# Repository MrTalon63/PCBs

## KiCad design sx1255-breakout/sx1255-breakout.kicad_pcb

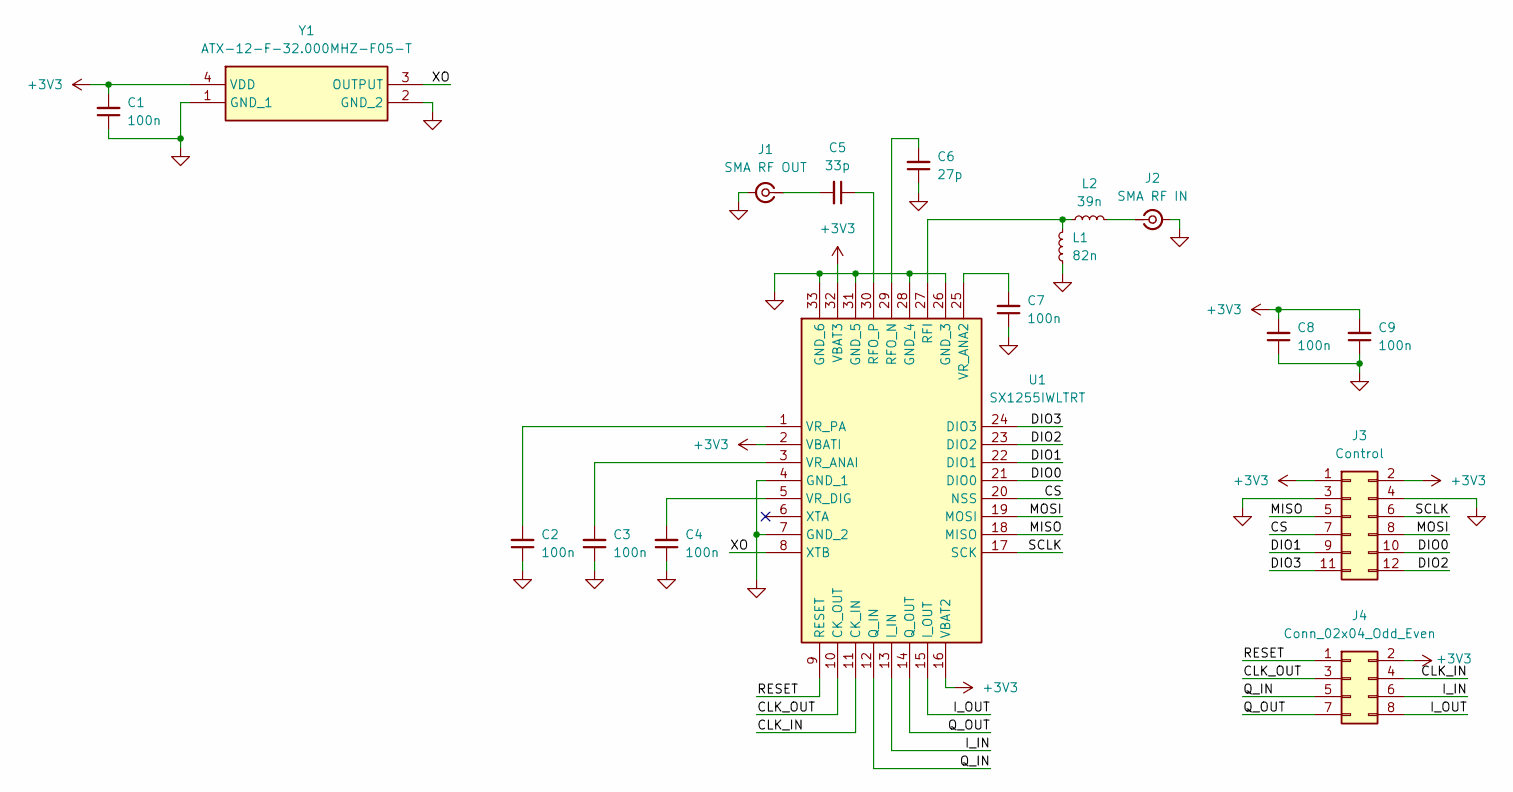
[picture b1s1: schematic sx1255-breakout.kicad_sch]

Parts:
C1, C2, C3, C4, C7, C8, C9: 100n; C_0402_1005Metric
C5: 33p; C_0402_1005Metric
C6: 27p; C_0402_1005Metric
J1: SMA RF OUT; SMA_Samtec_SMA-J-P-H-ST-EM1_EdgeMount
J2: SMA RF IN; SMA_Samtec_SMA-J-P-H-ST-EM1_EdgeMount
J3: Control; PinSocket_2x06_P2.54mm_Vertical
J4: Conn_02x04_Odd_Even; PinSocket_2x04_P2.54mm_Vertical
L1: 82n; L_0402_1005Metric
L2: 39n; L_0402_1005Metric
U1: SX1255IWLTRT; QFN50P500X500X80-33N-D; Mouser Part Number 947-SX1255IWLTRT
Y1: ATX-12-F-32.000MHZ-F05-T; ATX12F32000MHZF05T; Mouser Part Number 815-ATX12F32000MF05T

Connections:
+3V3: C1.2, C8.2, C9.2, J3.1, J3.2, J4.2, U1.2 (VBATI), U1.16 (VBAT2), U1.32 (VBAT3), Y1.4 (VDD)
/CLK_IN: J4.4, U1.11 (CK_IN)
/CLK_OUT: J4.3, U1.10 (CK_OUT)
/CS: J3.7, U1.20 (NSS)
/DIO0: J3.10, U1.21 (DIO0)
/DIO1: J3.9, U1.22 (DIO1)
/DIO2: J3.12, U1.23 (DIO2)
/DIO3: J3.11, U1.24 (DIO3)
/I_IN: J4.6, U1.13 (I_IN)
/I_OUT: J4.8, U1.15 (I_OUT)
/MISO: J3.5, U1.18 (MISO)
/MOSI: J3.8, U1.19 (MOSI)
/Q_IN: J4.5, U1.12 (Q_IN)
/Q_OUT: J4.7, U1.14 (Q_OUT)
/RESET: J4.1, U1.9 (RESET)
/SCLK: J3.6, U1.17 (SCK)
/XO: U1.8 (XTB), Y1.3 (OUTPUT)
GND: C1.1, C2.1, C3.1, C4.1, C6.1, C7.1, C8.1, C9.1, J1.2 (Ext), J2.2 (Ext), J3.3, J3.4, L1.1, U1.4 (GND_1), U1.7 (GND_2), U1.26 (GND_3), U1.28 (GND_4), U1.31 (GND_5), U1.33 (GND_6), Y1.1 (GND_1), Y1.2 (GND_2)
unnamed: C5.2, J1.1 (In)
unnamed: J2.1 (In), L2.2
unnamed: L1.2, L2.1, U1.27 (RFI)
unnamed: C6.2, U1.29 (RFO_N)
unnamed: C5.1, U1.30 (RFO_P)
unnamed: C7.2, U1.25 (VR_ANA2)
unnamed: C3.2, U1.3 (VR_ANAI)
unnamed: C4.2, U1.5 (VR_DIG)
unnamed: C2.2, U1.1 (VR_PA)

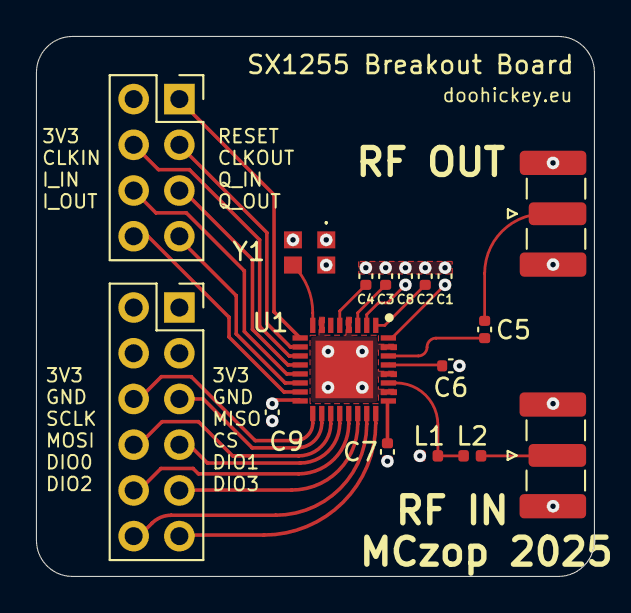
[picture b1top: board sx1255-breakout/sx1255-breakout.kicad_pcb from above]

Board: 6 copper layers, 31.0 x 30.0 mm, 17 parts (0 on the bottom side), 27 nets.

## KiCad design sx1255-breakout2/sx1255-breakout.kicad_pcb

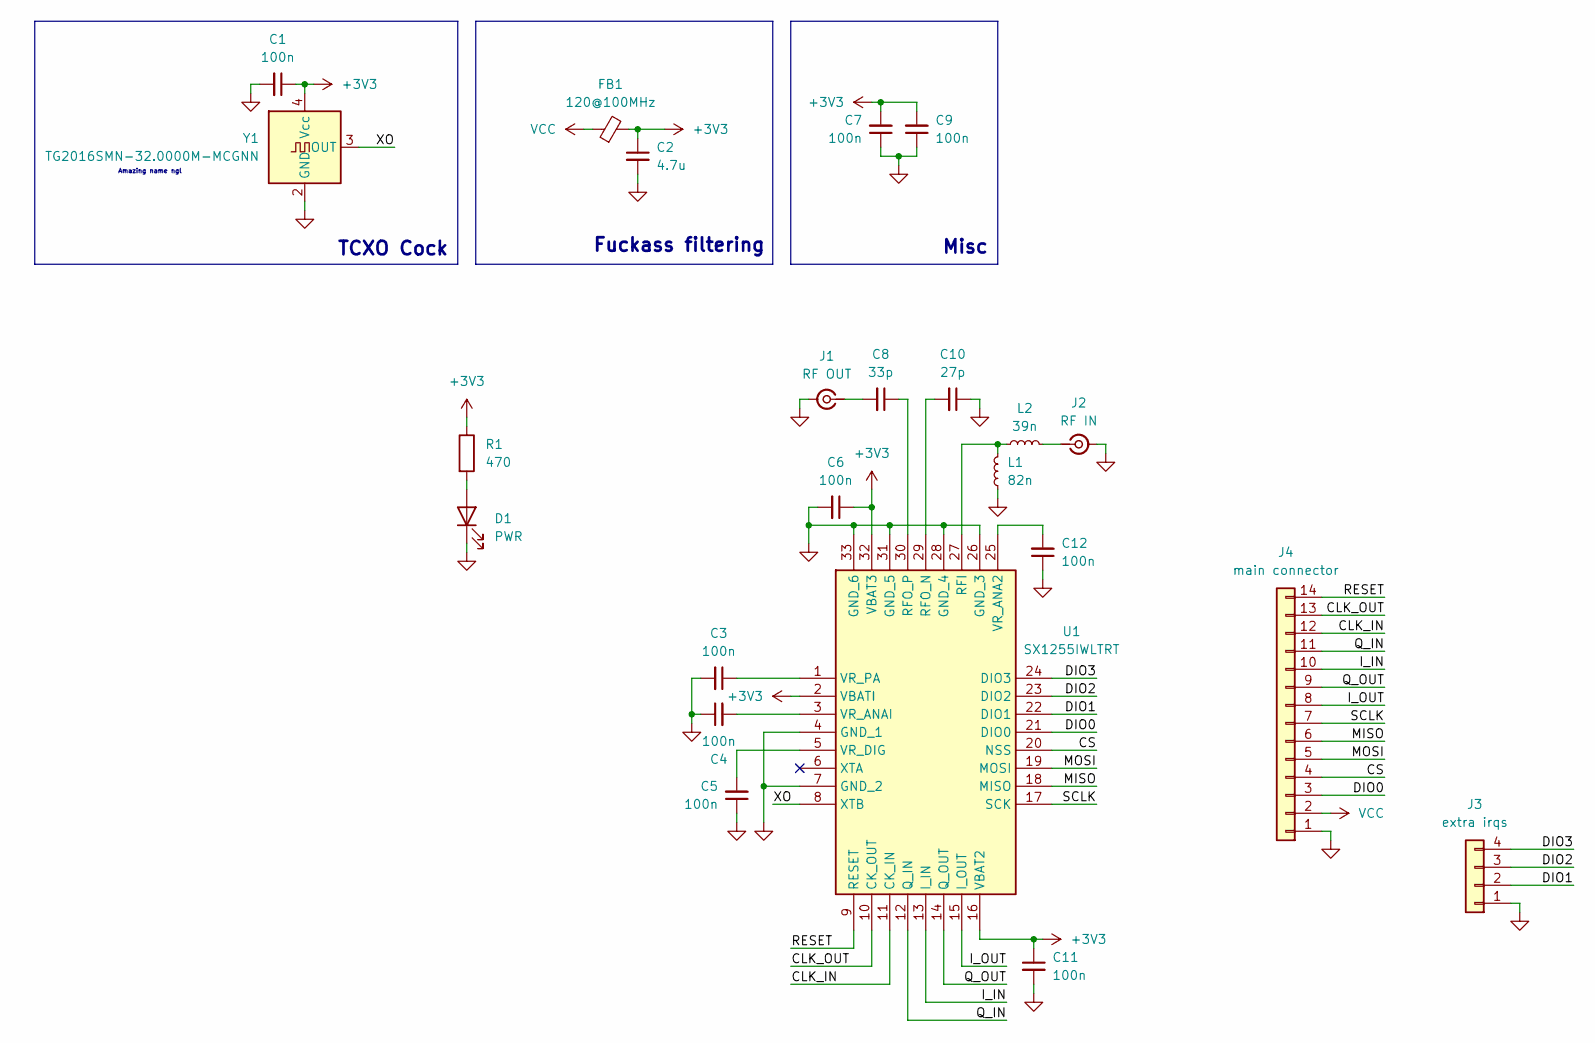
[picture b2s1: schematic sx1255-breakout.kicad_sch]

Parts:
C1, C3, C4, C5, C6, C7, C9, C11, C12: 100n; C_0603_1608Metric_Pad1.08x0.95mm_HandSolder
C2: 4.7u; C_0805_2012Metric_Pad1.18x1.45mm_HandSolder
C8: 33p; C_0603_1608Metric_Pad1.08x0.95mm_HandSolder
C10: 27p; C_0603_1608Metric_Pad1.08x0.95mm_HandSolder
D1: PWR; LED_0805_2012Metric_Pad1.15x1.40mm_HandSolder
FB1: 120@100MHz; L_0603_1608Metric_Pad1.05x0.95mm_HandSolder
J1: RF OUT; SMA_Samtec_SMA-J-P-H-ST-EM1_EdgeMount
J2: RF IN; SMA_Samtec_SMA-J-P-H-ST-EM1_EdgeMount
J3: extra irqs; PinHeader_1x04_P2.54mm_Vertical
J4: main connector; PinHeader_1x14_P2.54mm_Vertical
L1: 82n; L_0603_1608Metric_Pad1.05x0.95mm_HandSolder
L2: 39n; L_0603_1608Metric_Pad1.05x0.95mm_HandSolder
R1: 470; R_0603_1608Metric_Pad0.98x0.95mm_HandSolder
U1: SX1255IWLTRT; QFN-32-1EP_5x5mm_P0.5mm_EP3.1x3.1mm; Mouser Part Number 947-SX1255IWLTRT
Y1: TG2016SMN-32.0000M-MCGNN; Crystal_SMD_2016-4Pin_2.0x1.6mm

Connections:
+3V3: C1.1, C2.1, C6.1, C7.2, C9.2, C11.1, FB1.2, R1.1, U1.2 (VBATI), U1.16 (VBAT2), U1.32 (VBAT3), Y1.4 (Vcc)
/CLK_IN: J4.12, U1.11 (CK_IN)
/CLK_OUT: J4.13, U1.10 (CK_OUT)
/CS: J4.4, U1.20 (NSS)
/DIO0: J4.3, U1.21 (DIO0)
/DIO1: J3.2, U1.22 (DIO1)
/DIO2: J3.3, U1.23 (DIO2)
/DIO3: J3.4, U1.24 (DIO3)
/I_IN: J4.10, U1.13 (I_IN)
/I_OUT: J4.8, U1.15 (I_OUT)
/MISO: J4.6, U1.18 (MISO)
/MOSI: J4.5, U1.19 (MOSI)
/Q_IN: J4.11, U1.12 (Q_IN)
/Q_OUT: J4.9, U1.14 (Q_OUT)
/RESET: J4.14, U1.9 (RESET)
/SCLK: J4.7, U1.17 (SCK)
/XO: U1.8 (XTB), Y1.3 (OUT)
GND: C1.2, C2.2, C3.2, C4.1, C5.1, C6.2, C7.1, C9.1, C10.1, C11.2, C12.1, D1.1 (K), J1.2 (Ext), J2.2 (Ext), J3.1, J4.1, L1.1, U1.4 (GND_1), U1.7 (GND_2), U1.26 (GND_3), U1.28 (GND_4), U1.31 (GND_5), U1.33 (GND_6), Y1.2 (GND); also elsewhere on the board
unnamed 18: D1.2 (A), R1.2; also elsewhere on the board
unnamed: C8.2, J1.1 (In)
unnamed: J2.1 (In), L2.2
unnamed: L1.2, L2.1, U1.27 (RFI)
unnamed: C10.2, U1.29 (RFO_N)
unnamed: C8.1, U1.30 (RFO_P)
unnamed: C12.2, U1.25 (VR_ANA2)
unnamed: C4.2, U1.3 (VR_ANAI)
unnamed: C5.2, U1.5 (VR_DIG)
unnamed: C3.1, U1.1 (VR_PA)
VCC: FB1.1, J4.2

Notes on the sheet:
Misc
Amazing name ngl
Fuckass filtering
TCXO Cock

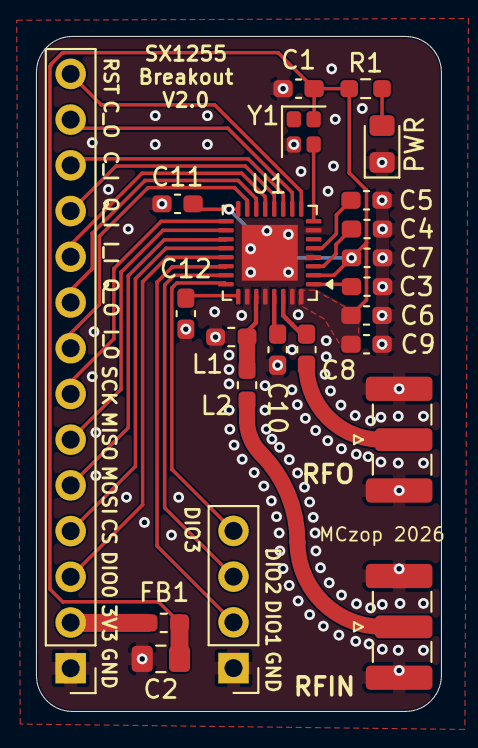
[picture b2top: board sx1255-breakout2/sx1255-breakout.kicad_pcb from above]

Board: 2 copper layers, 22.5 x 37.5 mm, 23 parts (0 on the bottom side), 29 nets.

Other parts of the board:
PWR: PWR; LED_0805_2012Metric_Pad1.15x1.40mm_HandSolder

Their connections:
GND: PWR.1 (K); also elsewhere on the board
unnamed 18: PWR.2 (A); also elsewhere on the board

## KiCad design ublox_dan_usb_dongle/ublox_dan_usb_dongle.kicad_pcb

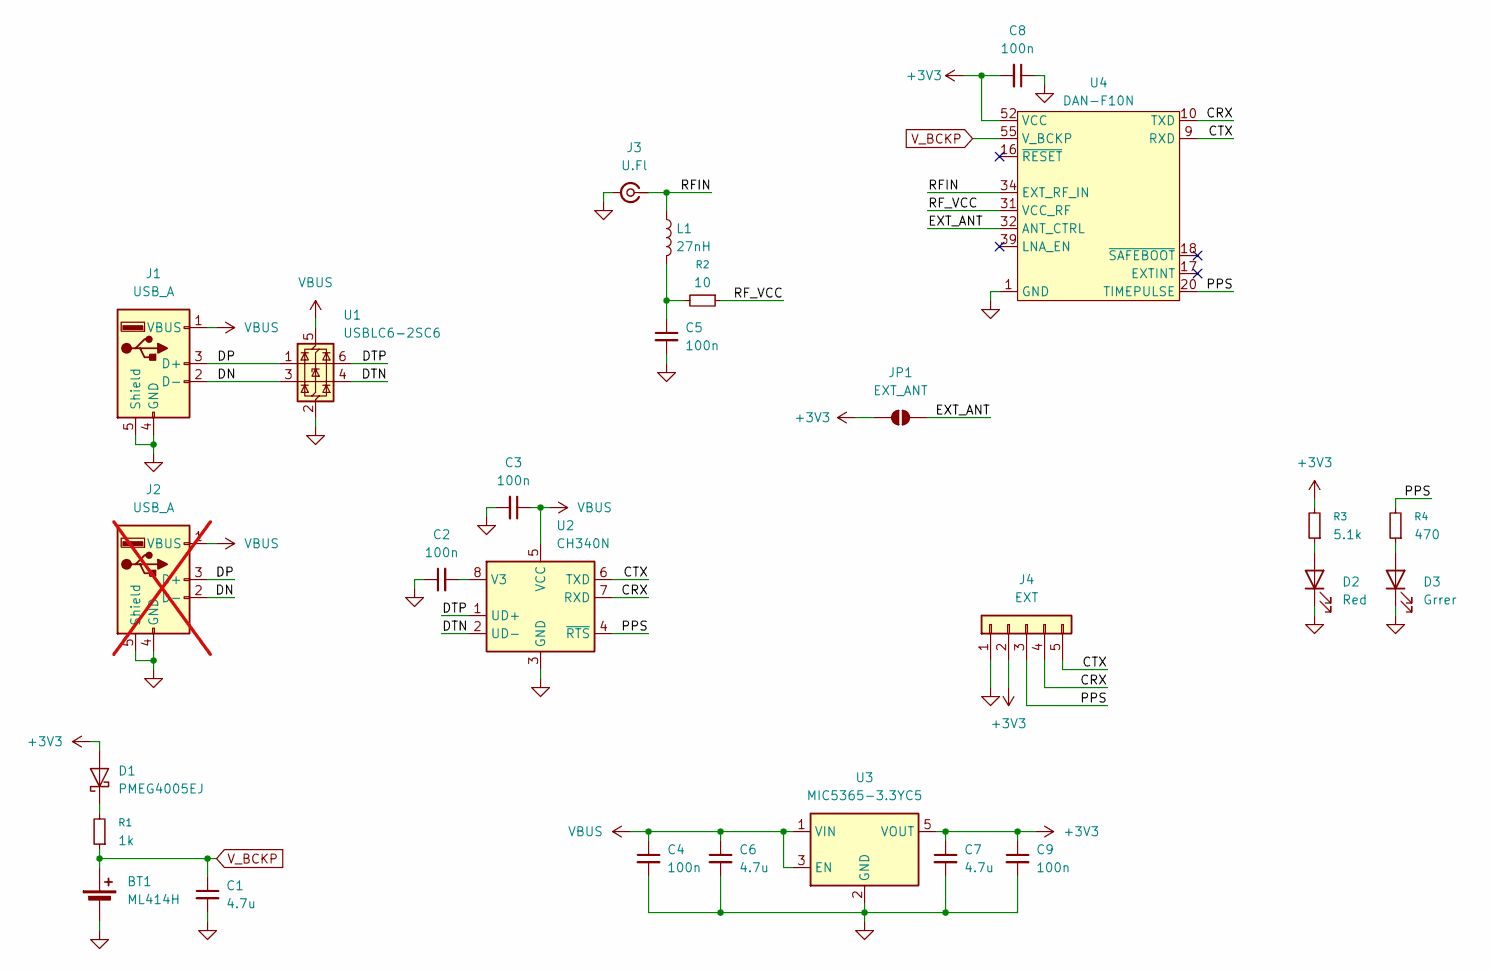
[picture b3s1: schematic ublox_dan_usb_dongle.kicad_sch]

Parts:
BT1: ML414H; ML414H_IV01E
C1, C6, C7: 4.7u; C_0603_1608Metric_Pad1.08x0.95mm_HandSolder
C2, C3, C4, C5, C8, C9: 100n; C_0603_1608Metric_Pad1.08x0.95mm_HandSolder
D1: PMEG4005EJ; D_SOD-323F
D2: Red; LED_0805_2012Metric
D3: Grrer; LED_0805_2012Metric
J1: USB_A; USB_A_Molex_48037-2200_Horizontal
J2: USB_A; USB_A_Molex_48037-2200_Horizontal; not fitted
J3: U.Fl; U.FL_Molex_MCRF_73412-0110_Vertical
J4: EXT; PinSocket_1x05_P1.27mm_Vertical
JP1: EXT_ANT; SolderJumper-2_P1.3mm_Open_RoundedPad1.0x1.5mm
L1: 27nH; L_0603_1608Metric
R1: 1k; R_0603_1608Metric_Pad0.98x0.95mm_HandSolder
R2: 10; R_0603_1608Metric_Pad0.98x0.95mm_HandSolder
R3: 5.1k; R_0603_1608Metric_Pad0.98x0.95mm_HandSolder
R4: 470; R_0603_1608Metric_Pad0.98x0.95mm_HandSolder
U1: USBLC6-2SC6; SOT-23-6_Handsoldering
U2: CH340N; JEITA_SOIC-8_3.9x4.9mm_P1.27mm
U3: MIC5365-3.3YC5; SOT-353_SC-70-5
U4: DAN-F10N

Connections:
+3V3: C7.1, C8.2, C9.1, D1.2 (A), J4.2, JP1.1 (A), R3.2, U3.5 (VOUT), U4.52 (VCC), U4.53 (VCC)
/CRX: J4.4, U2.7 (RXD), U4.10 (TXD)
/CTX: J4.5, U2.6 (TXD), U4.9 (RXD)
/DN: J1.2 (D-), J2.2 (D-), U1.3 (I/O2)
/DP: J1.3 (D+), J2.3 (D+), U1.1 (I/O1)
/DTN: U1.4 (I/O2), U2.2 (UD-)
/DTP: U1.6 (I/O1), U2.1 (UD+)
/EXT_ANT: JP1.2 (B), U4.32 (ANT_CTRL)
/PPS: J4.3, R4.2, U2.4 (~RTS), U4.20 (TIMEPULSE)
/RFIN: J3.1 (In), L1.1, U4.34 (EXT_RF_IN)
/RF_VCC: R2.1, U4.31 (VCC_RF)
GND: BT1.2 (-), C1.2, C2.1, C3.2, C4.2, C5.2, C6.2, C7.2, C8.1, C9.2, D2.1 (K), D3.1 (K), J1.4 (GND), J1.5 (Shield), J2.4 (GND), J2.5 (Shield), J3.2 (Ext), J4.1, U1.2 (GND), U2.3 (GND), U3.2 (GND), U4.1 (GND), U4.2 (GND), U4.3 (GND), U4.4 (GND), U4.5 (GND), U4.6 (GND), U4.7 (GND), U4.8 (GND), U4.13 (GND), U4.14 (GND), U4.15 (GND), U4.19 (GND), U4.21 (GND), U4.22 (GND), U4.23 (GND), U4.26 (GND), U4.27 (GND), U4.28 (GND), U4.29 (GND), U4.30 (GND), U4.33 (GND), U4.35 (GND), U4.37 (GND), U4.38 (GND), U4.40 (GND), U4.41 (GND), U4.42 (GND), U4.43 (GND), U4.44 (GND), U4.47 (GND), U4.48 (GND), U4.49 (GND), U4.50 (GND), U4.51 (GND), U4.54 (GND), U4.56 (GND), U4.57 (GND)
unnamed: C5.1, L1.2, R2.2
unnamed: D1.1 (K), R1.2
unnamed: D2.2 (A), R3.1
unnamed: D3.2 (A), R4.1
unnamed: C2.2, U2.8 (V3)
VBUS: C3.1, C4.1, C6.1, J1.1 (VBUS), J2.1 (VBUS), U1.5 (VBUS), U2.5 (VCC), U3.1 (VIN), U3.3 (EN)
V_BCKP: BT1.1 (+), C1.1, R1.1, U4.55 (V_BCKP)

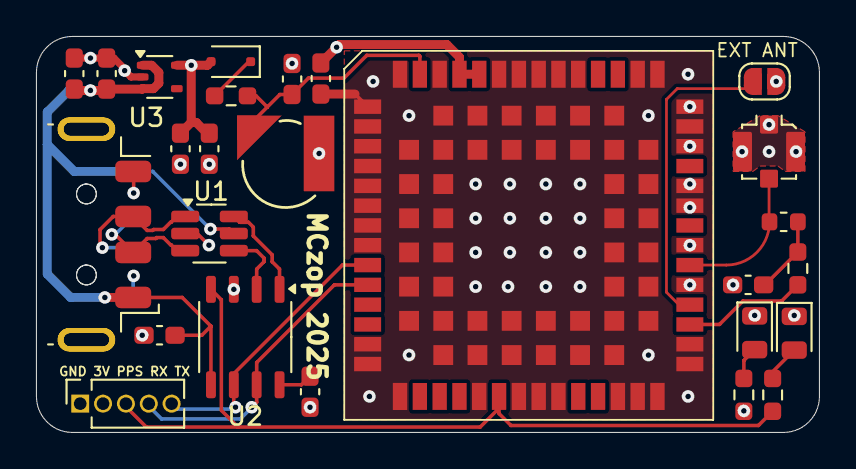
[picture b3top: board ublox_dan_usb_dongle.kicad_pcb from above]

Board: 6 copper layers, 43.5 x 22.0 mm, 27 parts (1 on the bottom side), 19 nets.

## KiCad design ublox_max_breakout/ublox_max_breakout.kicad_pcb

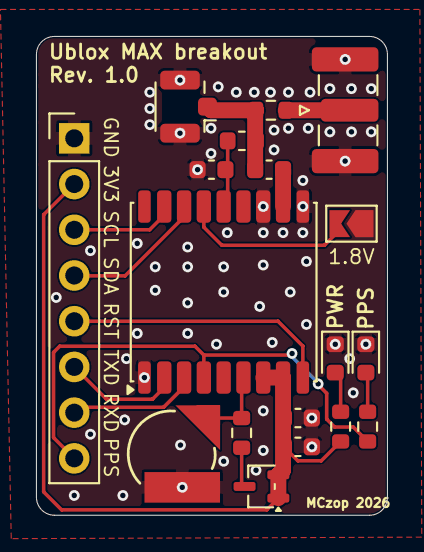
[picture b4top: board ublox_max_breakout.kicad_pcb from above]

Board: 2 copper layers, 19.5 x 26.6 mm, 18 parts (0 on the bottom side), 17 nets.

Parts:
BT1: ML414H; ML414H_IV01E
C1: 100p; C_0603_1608Metric
C2, C3, C4: 100n; C_0603_1608Metric
D1: BAT54CW; SOT-323_SC-70
J1: U.Fl; U.FL_Hirose_U.FL-R-SMT-1_Vertical
J2: SMA; SMA_Samtec_SMA-J-P-H-ST-EM1_EdgeMount
J3: Conn_01x08; PinHeader_1x08_P2.54mm_Vertical
JP1: VIOSEL; SolderJumper-2_P1.3mm_Open_TrianglePad1.0x1.5mm
L1: 56n; L_0603_1608Metric
PPS: PPS; LED_0603_1608Metric
PWR: PWR; LED_0603_1608Metric
R1: 0; R_0603_1608Metric
R2: 2k; R_0603_1608Metric
R3, R4: 270; R_0603_1608Metric
U1: MAX-M10S; ublox_MAX

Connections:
+3V3: C3.1, C4.1, D1.1, D1.2, J3.2, R3.1, U1.7 (VCC_IO), U1.8 (VCC)
/PPS: J3.8, R4.1, U1.4 (TIMEPULSE)
/RESET: J3.5, U1.9 (~RESET)
/RXD: J3.7, U1.3 (RXD)
/SCL: J3.3, U1.17 (SCL)
/SDA: J3.4, U1.16 (SDA)
/TXD: J3.6, U1.2 (TXD)
GND: BT1.-, C2.2, C3.2, C4.2, J1.2 (Ext), J2.2 (Ext), J3.1, JP1.1 (A), PPS.1 (K), PWR.1 (K), U1.1 (GND), U1.10 (GND), U1.12 (GND)
unnamed: D1.3, R2.1
unnamed: C1.1, J1.1 (In), L1.2, R1.1
unnamed: J2.1 (In), R1.2
unnamed: JP1.2 (B), U1.15 (VIO_SEL)
unnamed: PWR.2 (A), R3.2
unnamed: PPS.2 (A), R4.2
unnamed: C1.2, U1.11 (RF_IN)
unnamed: C2.1, L1.1, U1.14 (VCC_RF)
unnamed: BT1.+, R2.2, U1.6 (V_BCKP)

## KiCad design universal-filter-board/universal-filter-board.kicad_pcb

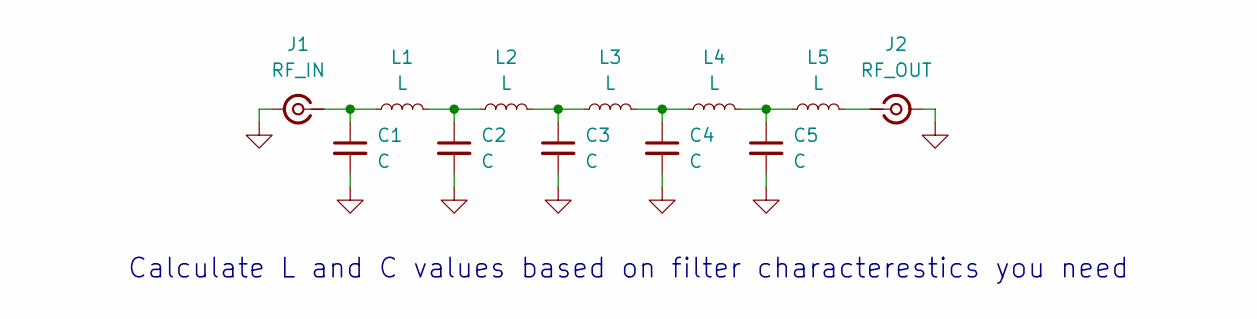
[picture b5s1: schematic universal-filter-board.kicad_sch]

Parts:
C1, C2, C3, C4, C5: C; C_0603_1608Metric_Pad1.08x0.95mm_HandSolder
J1: RF_IN; SMA_Samtec_SMA-J-P-H-ST-EM1_EdgeMount
J2: RF_OUT; SMA_Samtec_SMA-J-P-H-ST-EM1_EdgeMount
L1, L2, L3, L4, L5: L; L_0603_1608Metric_Pad1.05x0.95mm_HandSolder

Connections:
GND: C1.2, C2.2, C3.2, C4.2, C5.2, J1.2 (Ext), J2.2 (Ext)
unnamed: C2.1, L1.2, L2.1
unnamed: C3.1, L2.2, L3.1
unnamed: C4.1, L3.2, L4.1
unnamed: C5.1, L4.2, L5.1
unnamed: C1.1, J1.1 (In), L1.1
unnamed: J2.1 (In), L5.2

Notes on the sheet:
Calculate L and C values based on filter characterestics you need

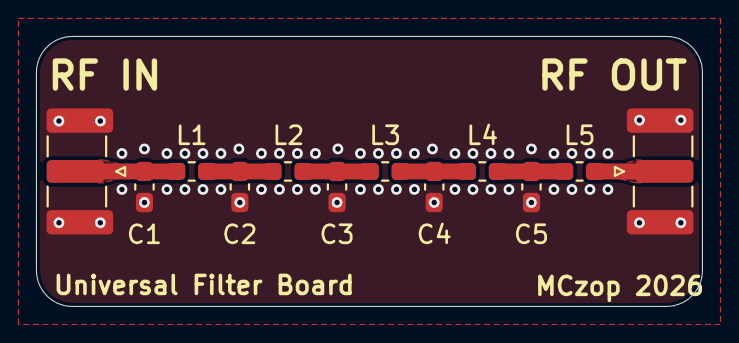
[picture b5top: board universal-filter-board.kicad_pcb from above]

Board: 2 copper layers, 37.0 x 15.0 mm, 12 parts (0 on the bottom side), 7 nets.

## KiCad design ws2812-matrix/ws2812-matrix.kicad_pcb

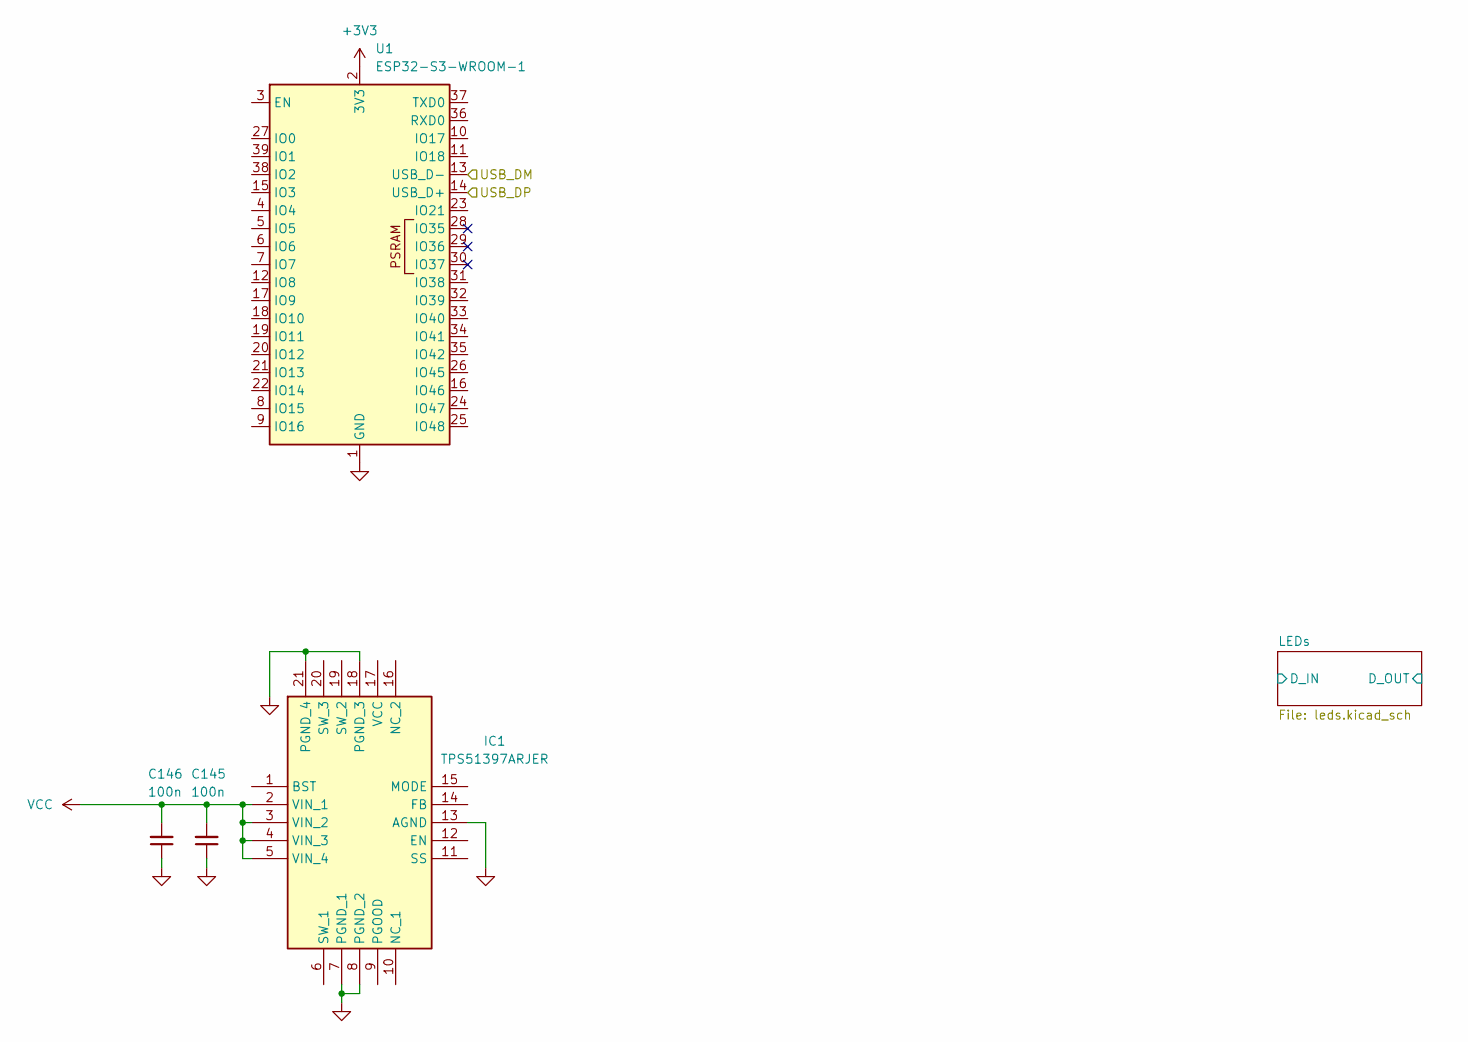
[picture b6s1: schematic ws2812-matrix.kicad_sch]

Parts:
C145, C146: 100n; C_0402_1005Metric
IC1: TPS51397ARJER; QFN45P300X300X100-21N-D; Mouser Part Number 595-TPS51397ARJER
U1: ESP32-S3-WROOM-1

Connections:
+3V3: U1.2 (3V3)
/USB_DM: U1.13 (USB_D-)
/USB_DP: U1.14 (USB_D+)
GND: C145.1, C146.1, IC1.7 (PGND_1), IC1.8 (PGND_2), IC1.13 (AGND), IC1.18 (PGND_3), IC1.21 (PGND_4), U1.1 (GND), U1.40 (GND), U1.41 (GND); also elsewhere on the board
VCC: C145.2, C146.2, IC1.2 (VIN_1), IC1.3 (VIN_2), IC1.4 (VIN_3), IC1.5 (VIN_4)

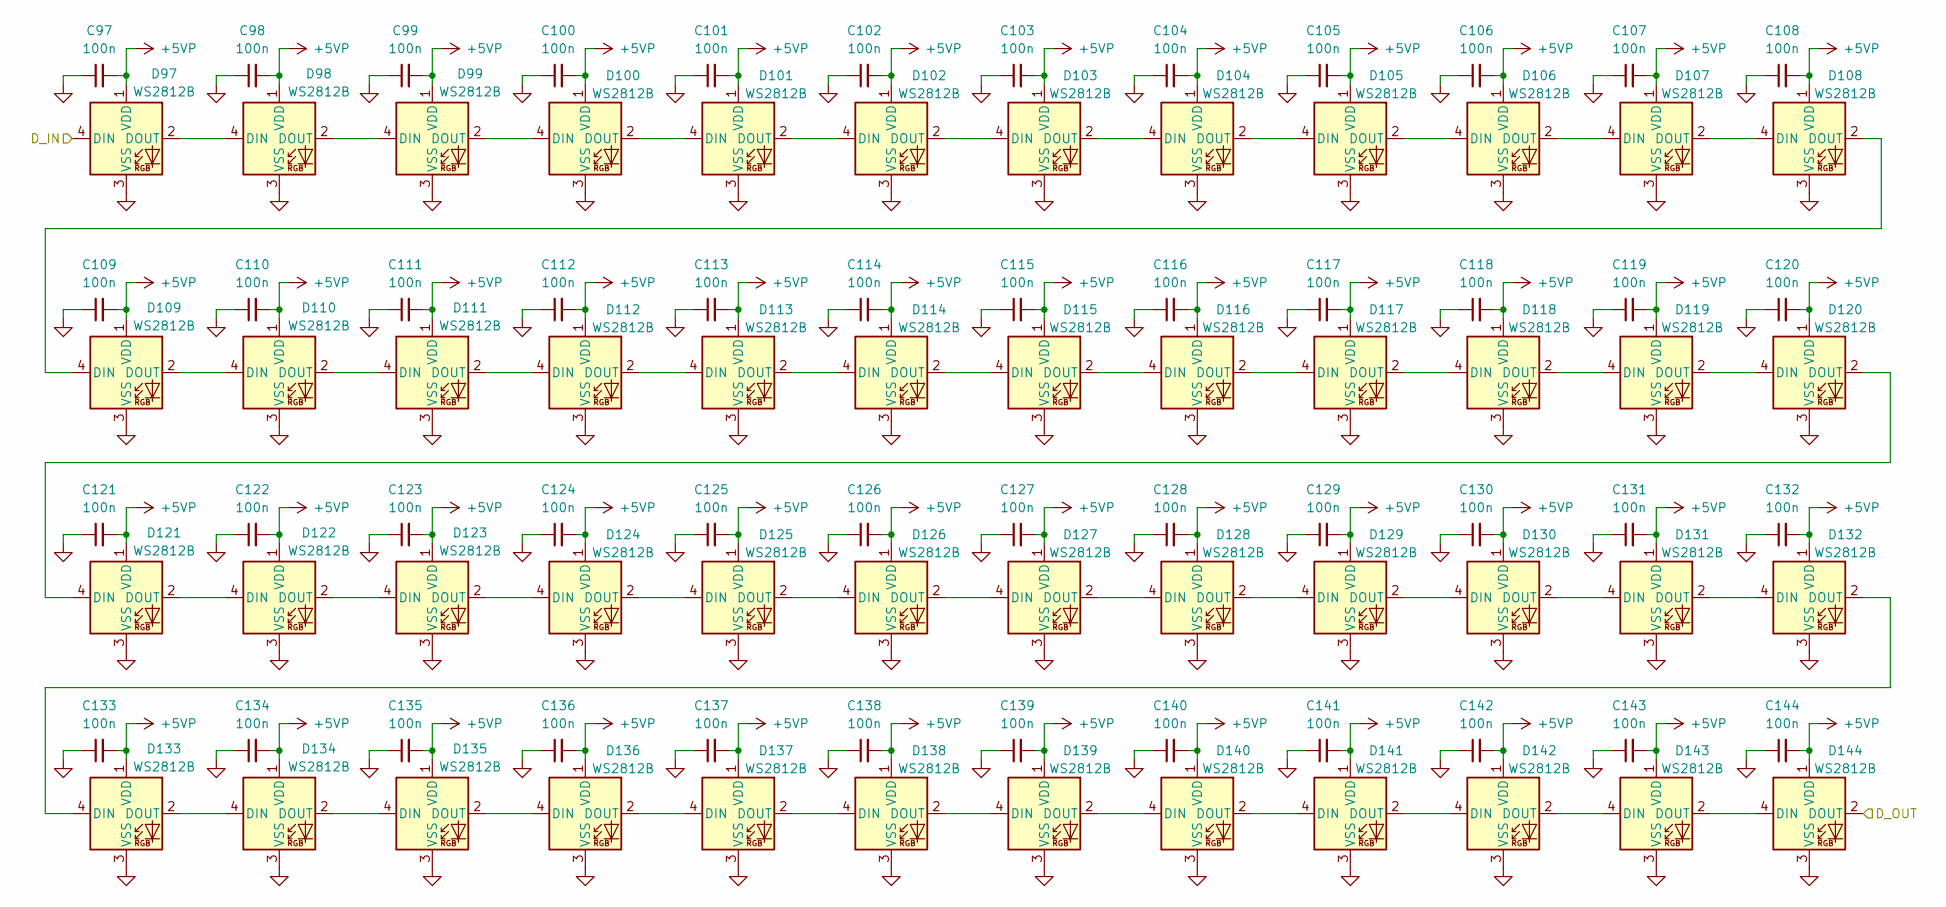
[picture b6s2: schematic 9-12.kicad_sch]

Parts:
C97, C98, C99, C100, C101, C102, C103, C104, C105, C106, C107, C108, C109, C110, C111, C112, C113, C114, C115, C116, C117, C118, C119, C120, C121, C122, C123, C124, C125, C126, C127, C128, C129, C130, C131, C132, C133, C134, C135, C136, C137, C138, C139, C140, C141, C142, C143, C144: 100n; C_0402_1005Metric
D97, D98, D99, D100, D101, D102, D103, D104, D105, D106, D107, D108, D109, D110, D111, D112, D113, D114, D115, D116, D117, D118, D119, D120, D121, D122, D123, D124, D125, D126, D127, D128, D129, D130, D131, D132, D133, D134, D135, D136, D137, D138, D139, D140, D141, D142, D143, D144: WS2812B; LED_WS2812B_PLCC4_5.0x5.0mm_P3.2mm

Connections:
+5VP: C97.2, C98.2, C99.2, C100.2, C101.2, C102.2, C103.2, C104.2, C105.2, C106.2, C107.2, C108.2, C109.2, C110.2, C111.2, C112.2, C113.2, C114.2, C115.2, C116.2, C117.2, C118.2, C119.2, C120.2, C121.2, C122.2, C123.2, C124.2, C125.2, C126.2, C127.2, C128.2, C129.2, C130.2, C131.2, C132.2, C133.2, C134.2, C135.2, C136.2, C137.2, C138.2, C139.2, C140.2, C141.2, C142.2, C143.2, C144.2, D97.1 (VDD), D98.1 (VDD), D99.1 (VDD), D100.1 (VDD), D101.1 (VDD), D102.1 (VDD), D103.1 (VDD), D104.1 (VDD), D105.1 (VDD), D106.1 (VDD), D107.1 (VDD), D108.1 (VDD), D109.1 (VDD), D110.1 (VDD), D111.1 (VDD), D112.1 (VDD), D113.1 (VDD), D114.1 (VDD), D115.1 (VDD), D116.1 (VDD), D117.1 (VDD), D118.1 (VDD), D119.1 (VDD), D120.1 (VDD), D121.1 (VDD), D122.1 (VDD), D123.1 (VDD), D124.1 (VDD), D125.1 (VDD), D126.1 (VDD), D127.1 (VDD), D128.1 (VDD), D129.1 (VDD), D130.1 (VDD), D131.1 (VDD), D132.1 (VDD), D133.1 (VDD), D134.1 (VDD), D135.1 (VDD), D136.1 (VDD), D137.1 (VDD), D138.1 (VDD), D139.1 (VDD), D140.1 (VDD), D141.1 (VDD), D142.1 (VDD), D143.1 (VDD), D144.1 (VDD); also elsewhere on the board
/LEDs/5-8/D_OUT: D97.4 (DIN); also elsewhere on the board
/LEDs/D_OUT: D144.2 (DOUT)
GND: C97.1, C98.1, C99.1, C100.1, C101.1, C102.1, C103.1, C104.1, C105.1, C106.1, C107.1, C108.1, C109.1, C110.1, C111.1, C112.1, C113.1, C114.1, C115.1, C116.1, C117.1, C118.1, C119.1, C120.1, C121.1, C122.1, C123.1, C124.1, C125.1, C126.1, C127.1, C128.1, C129.1, C130.1, C131.1, C132.1, C133.1, C134.1, C135.1, C136.1, C137.1, C138.1, C139.1, C140.1, C141.1, C142.1, C143.1, C144.1, D97.3 (VSS), D98.3 (VSS), D99.3 (VSS), D100.3 (VSS), D101.3 (VSS), D102.3 (VSS), D103.3 (VSS), D104.3 (VSS), D105.3 (VSS), D106.3 (VSS), D107.3 (VSS), D108.3 (VSS), D109.3 (VSS), D110.3 (VSS), D111.3 (VSS), D112.3 (VSS), D113.3 (VSS), D114.3 (VSS), D115.3 (VSS), D116.3 (VSS), D117.3 (VSS), D118.3 (VSS), D119.3 (VSS), D120.3 (VSS), D121.3 (VSS), D122.3 (VSS), D123.3 (VSS), D124.3 (VSS), D125.3 (VSS), D126.3 (VSS), D127.3 (VSS), D128.3 (VSS), D129.3 (VSS), D130.3 (VSS), D131.3 (VSS), D132.3 (VSS), D133.3 (VSS), D134.3 (VSS), D135.3 (VSS), D136.3 (VSS), D137.3 (VSS), D138.3 (VSS), D139.3 (VSS), D140.3 (VSS), D141.3 (VSS), D142.3 (VSS), D143.3 (VSS), D144.3 (VSS); also elsewhere on the board
unnamed: D97.2 (DOUT), D98.4 (DIN)
unnamed: D98.2 (DOUT), D99.4 (DIN)
unnamed: D99.2 (DOUT), D100.4 (DIN)
unnamed: D100.2 (DOUT), D101.4 (DIN)
unnamed: D101.2 (DOUT), D102.4 (DIN)
unnamed: D102.2 (DOUT), D103.4 (DIN)
unnamed: D103.2 (DOUT), D104.4 (DIN)
unnamed: D104.2 (DOUT), D105.4 (DIN)
unnamed: D105.2 (DOUT), D106.4 (DIN)
unnamed: D106.2 (DOUT), D107.4 (DIN)
unnamed: D107.2 (DOUT), D108.4 (DIN)
unnamed: D108.2 (DOUT), D109.4 (DIN)
unnamed: D109.2 (DOUT), D110.4 (DIN)
unnamed: D110.2 (DOUT), D111.4 (DIN)
unnamed: D111.2 (DOUT), D112.4 (DIN)
unnamed: D112.2 (DOUT), D113.4 (DIN)
unnamed: D113.2 (DOUT), D114.4 (DIN)
unnamed: D114.2 (DOUT), D115.4 (DIN)
unnamed: D115.2 (DOUT), D116.4 (DIN)
unnamed: D116.2 (DOUT), D117.4 (DIN)
unnamed: D117.2 (DOUT), D118.4 (DIN)
unnamed: D118.2 (DOUT), D119.4 (DIN)
unnamed: D119.2 (DOUT), D120.4 (DIN)
unnamed: D120.2 (DOUT), D121.4 (DIN)
unnamed: D121.2 (DOUT), D122.4 (DIN)
unnamed: D122.2 (DOUT), D123.4 (DIN)
unnamed: D123.2 (DOUT), D124.4 (DIN)
unnamed: D124.2 (DOUT), D125.4 (DIN)
unnamed: D125.2 (DOUT), D126.4 (DIN)
unnamed: D126.2 (DOUT), D127.4 (DIN)
unnamed: D127.2 (DOUT), D128.4 (DIN)
unnamed: D128.2 (DOUT), D129.4 (DIN)
unnamed: D129.2 (DOUT), D130.4 (DIN)
unnamed: D130.2 (DOUT), D131.4 (DIN)
unnamed: D131.2 (DOUT), D132.4 (DIN)
unnamed: D132.2 (DOUT), D133.4 (DIN)
unnamed: D133.2 (DOUT), D134.4 (DIN)
unnamed: D134.2 (DOUT), D135.4 (DIN)
unnamed: D135.2 (DOUT), D136.4 (DIN)
unnamed: D136.2 (DOUT), D137.4 (DIN)
unnamed: D137.2 (DOUT), D138.4 (DIN)
unnamed: D138.2 (DOUT), D139.4 (DIN)
unnamed: D139.2 (DOUT), D140.4 (DIN)
unnamed: D140.2 (DOUT), D141.4 (DIN)
unnamed: D141.2 (DOUT), D142.4 (DIN)
unnamed: D142.2 (DOUT), D143.4 (DIN)
unnamed: D143.2 (DOUT), D144.4 (DIN)

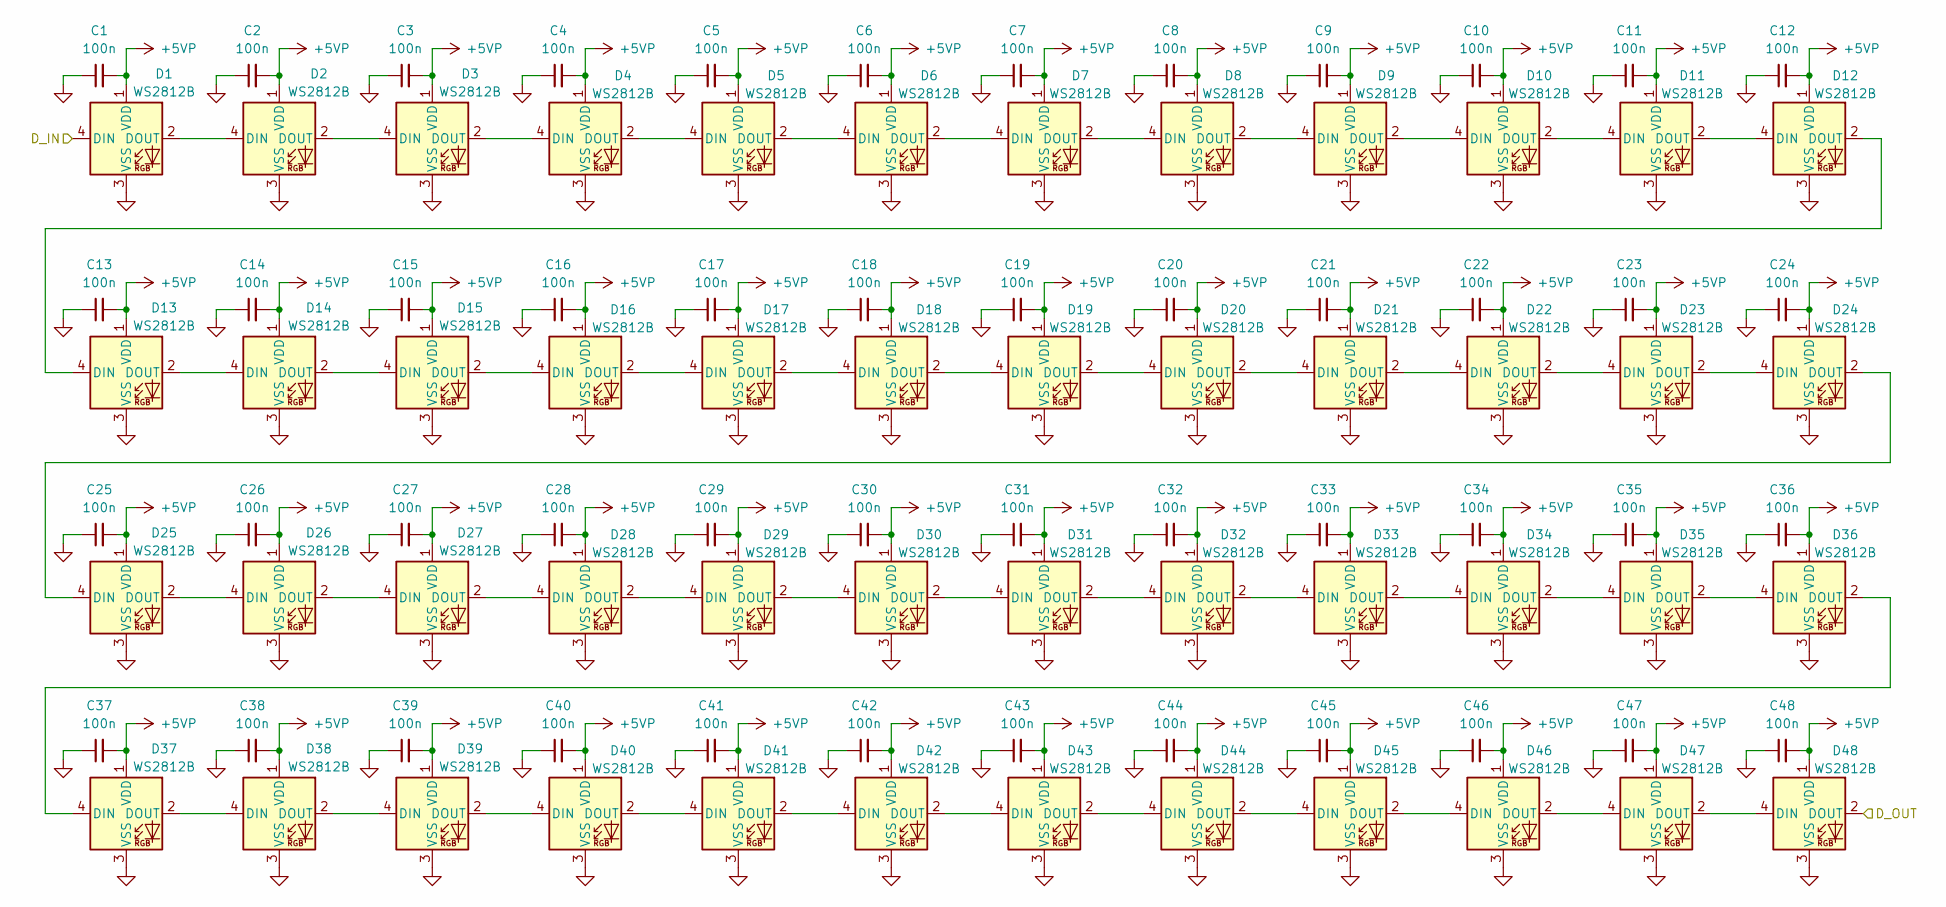
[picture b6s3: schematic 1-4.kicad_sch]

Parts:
C1, C2, C3, C4, C5, C6, C7, C8, C9, C10, C11, C12, C13, C14, C15, C16, C17, C18, C19, C20, C21, C22, C23, C24, C25, C26, C27, C28, C29, C30, C31, C32, C33, C34, C35, C36, C37, C38, C39, C40, C41, C42, C43, C44, C45, C46, C47, C48: 100n; C_0402_1005Metric
D1, D2, D3, D4, D5, D6, D7, D8, D9, D10, D11, D12, D13, D14, D15, D16, D17, D18, D19, D20, D21, D22, D23, D24, D25, D26, D27, D28, D29, D30, D31, D32, D33, D34, D35, D36, D37, D38, D39, D40, D41, D42, D43, D44, D45, D46, D47, D48: WS2812B; LED_WS2812B_PLCC4_5.0x5.0mm_P3.2mm

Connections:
+5VP: C1.2, C2.2, C3.2, C4.2, C5.2, C6.2, C7.2, C8.2, C9.2, C10.2, C11.2, C12.2, C13.2, C14.2, C15.2, C16.2, C17.2, C18.2, C19.2, C20.2, C21.2, C22.2, C23.2, C24.2, C25.2, C26.2, C27.2, C28.2, C29.2, C30.2, C31.2, C32.2, C33.2, C34.2, C35.2, C36.2, C37.2, C38.2, C39.2, C40.2, C41.2, C42.2, C43.2, C44.2, C45.2, C46.2, C47.2, C48.2, D1.1 (VDD), D2.1 (VDD), D3.1 (VDD), D4.1 (VDD), D5.1 (VDD), D6.1 (VDD), D7.1 (VDD), D8.1 (VDD), D9.1 (VDD), D10.1 (VDD), D11.1 (VDD), D12.1 (VDD), D13.1 (VDD), D14.1 (VDD), D15.1 (VDD), D16.1 (VDD), D17.1 (VDD), D18.1 (VDD), D19.1 (VDD), D20.1 (VDD), D21.1 (VDD), D22.1 (VDD), D23.1 (VDD), D24.1 (VDD), D25.1 (VDD), D26.1 (VDD), D27.1 (VDD), D28.1 (VDD), D29.1 (VDD), D30.1 (VDD), D31.1 (VDD), D32.1 (VDD), D33.1 (VDD), D34.1 (VDD), D35.1 (VDD), D36.1 (VDD), D37.1 (VDD), D38.1 (VDD), D39.1 (VDD), D40.1 (VDD), D41.1 (VDD), D42.1 (VDD), D43.1 (VDD), D44.1 (VDD), D45.1 (VDD), D46.1 (VDD), D47.1 (VDD), D48.1 (VDD); also elsewhere on the board
/LEDs/1-4/D_OUT: D48.2 (DOUT); also elsewhere on the board
/LEDs/D_IN: D1.4 (DIN)
GND: C1.1, C2.1, C3.1, C4.1, C5.1, C6.1, C7.1, C8.1, C9.1, C10.1, C11.1, C12.1, C13.1, C14.1, C15.1, C16.1, C17.1, C18.1, C19.1, C20.1, C21.1, C22.1, C23.1, C24.1, C25.1, C26.1, C27.1, C28.1, C29.1, C30.1, C31.1, C32.1, C33.1, C34.1, C35.1, C36.1, C37.1, C38.1, C39.1, C40.1, C41.1, C42.1, C43.1, C44.1, C45.1, C46.1, C47.1, C48.1, D1.3 (VSS), D2.3 (VSS), D3.3 (VSS), D4.3 (VSS), D5.3 (VSS), D6.3 (VSS), D7.3 (VSS), D8.3 (VSS), D9.3 (VSS), D10.3 (VSS), D11.3 (VSS), D12.3 (VSS), D13.3 (VSS), D14.3 (VSS), D15.3 (VSS), D16.3 (VSS), D17.3 (VSS), D18.3 (VSS), D19.3 (VSS), D20.3 (VSS), D21.3 (VSS), D22.3 (VSS), D23.3 (VSS), D24.3 (VSS), D25.3 (VSS), D26.3 (VSS), D27.3 (VSS), D28.3 (VSS), D29.3 (VSS), D30.3 (VSS), D31.3 (VSS), D32.3 (VSS), D33.3 (VSS), D34.3 (VSS), D35.3 (VSS), D36.3 (VSS), D37.3 (VSS), D38.3 (VSS), D39.3 (VSS), D40.3 (VSS), D41.3 (VSS), D42.3 (VSS), D43.3 (VSS), D44.3 (VSS), D45.3 (VSS), D46.3 (VSS), D47.3 (VSS), D48.3 (VSS); also elsewhere on the board
unnamed: D1.2 (DOUT), D2.4 (DIN)
unnamed: D2.2 (DOUT), D3.4 (DIN)
unnamed: D3.2 (DOUT), D4.4 (DIN)
unnamed: D4.2 (DOUT), D5.4 (DIN)
unnamed: D5.2 (DOUT), D6.4 (DIN)
unnamed: D6.2 (DOUT), D7.4 (DIN)
unnamed: D7.2 (DOUT), D8.4 (DIN)
unnamed: D8.2 (DOUT), D9.4 (DIN)
unnamed: D9.2 (DOUT), D10.4 (DIN)
unnamed: D10.2 (DOUT), D11.4 (DIN)
unnamed: D11.2 (DOUT), D12.4 (DIN)
unnamed: D12.2 (DOUT), D13.4 (DIN)
unnamed: D13.2 (DOUT), D14.4 (DIN)
unnamed: D14.2 (DOUT), D15.4 (DIN)
unnamed: D15.2 (DOUT), D16.4 (DIN)
unnamed: D16.2 (DOUT), D17.4 (DIN)
unnamed: D17.2 (DOUT), D18.4 (DIN)
unnamed: D18.2 (DOUT), D19.4 (DIN)
unnamed: D19.2 (DOUT), D20.4 (DIN)
unnamed: D20.2 (DOUT), D21.4 (DIN)
unnamed: D21.2 (DOUT), D22.4 (DIN)
unnamed: D22.2 (DOUT), D23.4 (DIN)
unnamed: D23.2 (DOUT), D24.4 (DIN)
unnamed: D24.2 (DOUT), D25.4 (DIN)
unnamed: D25.2 (DOUT), D26.4 (DIN)
unnamed: D26.2 (DOUT), D27.4 (DIN)
unnamed: D27.2 (DOUT), D28.4 (DIN)
unnamed: D28.2 (DOUT), D29.4 (DIN)
unnamed: D29.2 (DOUT), D30.4 (DIN)
unnamed: D30.2 (DOUT), D31.4 (DIN)
unnamed: D31.2 (DOUT), D32.4 (DIN)
unnamed: D32.2 (DOUT), D33.4 (DIN)
unnamed: D33.2 (DOUT), D34.4 (DIN)
unnamed: D34.2 (DOUT), D35.4 (DIN)
unnamed: D35.2 (DOUT), D36.4 (DIN)
unnamed: D36.2 (DOUT), D37.4 (DIN)
unnamed: D37.2 (DOUT), D38.4 (DIN)
unnamed: D38.2 (DOUT), D39.4 (DIN)
unnamed: D39.2 (DOUT), D40.4 (DIN)
unnamed: D40.2 (DOUT), D41.4 (DIN)
unnamed: D41.2 (DOUT), D42.4 (DIN)
unnamed: D42.2 (DOUT), D43.4 (DIN)
unnamed: D43.2 (DOUT), D44.4 (DIN)
unnamed: D44.2 (DOUT), D45.4 (DIN)
unnamed: D45.2 (DOUT), D46.4 (DIN)
unnamed: D46.2 (DOUT), D47.4 (DIN)
unnamed: D47.2 (DOUT), D48.4 (DIN)
